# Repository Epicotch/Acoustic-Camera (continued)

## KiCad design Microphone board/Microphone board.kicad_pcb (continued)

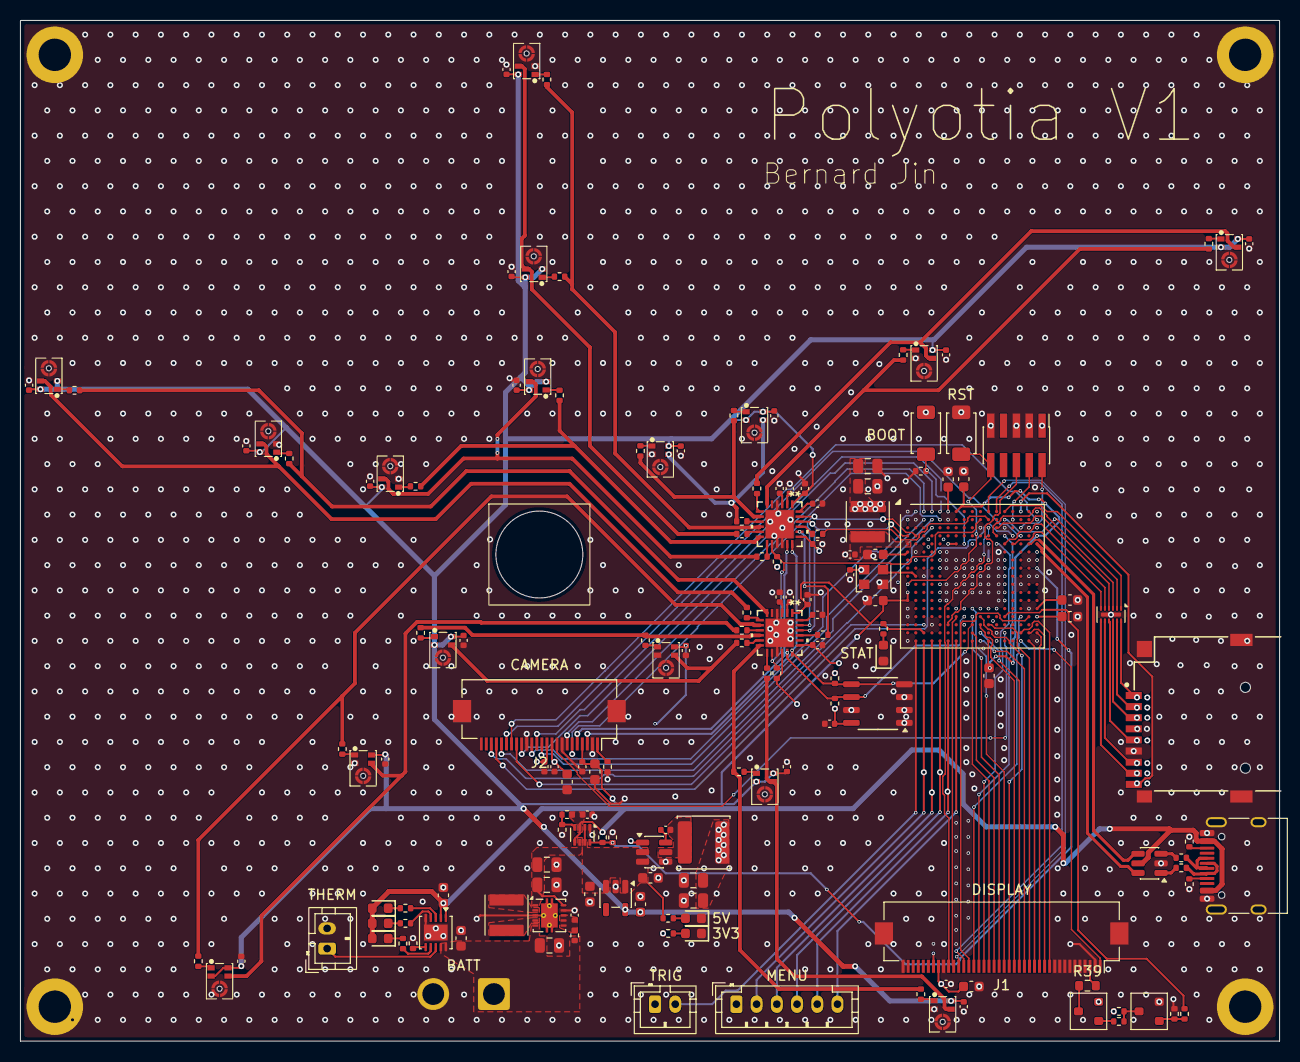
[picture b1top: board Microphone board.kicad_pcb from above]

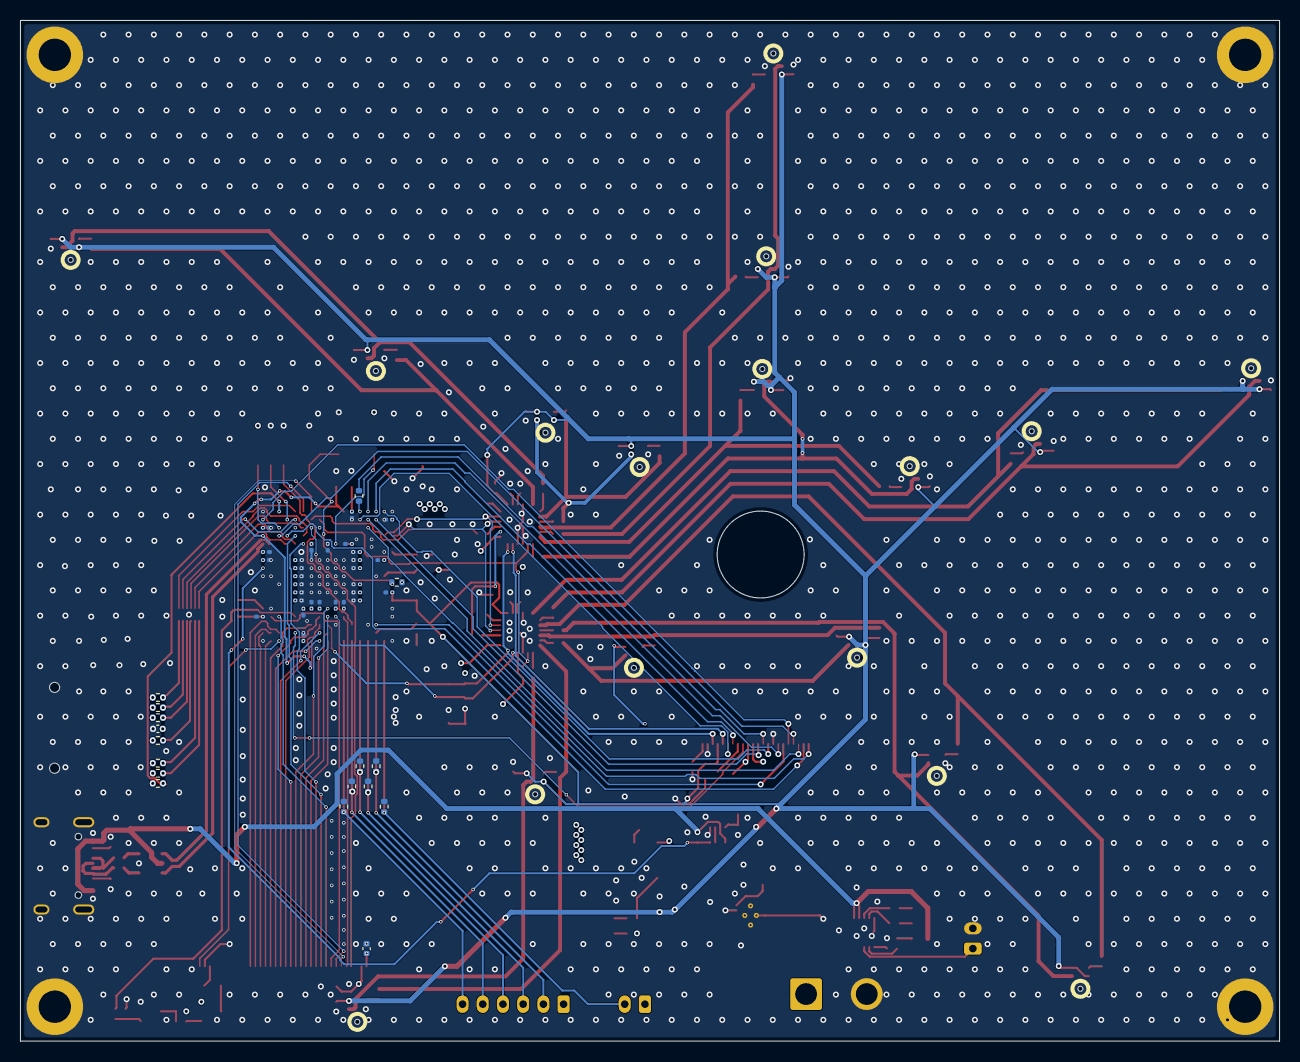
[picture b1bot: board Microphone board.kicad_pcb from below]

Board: 4 copper layers, 124.6 x 101.0 mm, 212 parts (46 on the bottom side), 161 nets.

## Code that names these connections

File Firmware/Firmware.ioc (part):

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Mcu.Name=STM32H747XIHx
Mcu.Package=TFBGA240
Mcu.UserName=STM32H747XIHx
PA0_C.GPIOParameters=PinAttribute
PA0_C.PinAttribute=CortexM4
PA0_C.Signal=ADCx_INP0
PA10.GPIOParameters=PinAttribute
PA10.Mode=Slave_8_bits_External_Synchro
PA10.PinAttribute=CortexM4
PA10.Signal=DCMI_D1
PA11.GPIOParameters=PinAttribute
PA11.Mode=Device_Only
PA11.PinAttribute=CortexM4
PA11.Signal=USB_OTG_FS_DM
PA12.GPIOParameters=PinAttribute
PA12.Mode=Device_Only
PA12.PinAttribute=CortexM4
PA12.Signal=USB_OTG_FS_DP
PA13\ (JTMS/SWDIO).GPIOParameters=PinAttribute
PA13\ (JTMS/SWDIO).Mode=Trace_Asynchronous_SW
PA13\ (JTMS/SWDIO).PinAttribute=CortexM7
PA13\ (JTMS/SWDIO).Signal=DEBUG_JTMS-SWDIO
PA14\ (JTCK/SWCLK).GPIOParameters=PinAttribute
PA14\ (JTCK/SWCLK).Mode=Trace_Asynchronous_SW
PA14\ (JTCK/SWCLK).PinAttribute=CortexM7
PA14\ (JTCK/SWCLK).Signal=DEBUG_JTCK-SWCLK
PA3.ContextOwner=CortexM4
PA3.GPIOParameters=GPIO_Label,PinAttribute
PA3.GPIO_Label=TRIGGER
PA3.PinAttribute=CortexM4
PA3.Signal=GPIO_Input
PA4.ContextOwner=CortexM4
PA4.GPIOParameters=GPIO_Label,PinAttribute
PA4.GPIO_Label=LEFT
PA4.PinAttribute=CortexM4
PA4.Signal=GPIO_Input
PA5.ContextOwner=CortexM4
PA5.GPIOParameters=GPIO_Label,PinAttribute
PA5.GPIO_Label=STATUS_LED
PA5.PinAttribute=CortexM4
PA5.Signal=GPIO_Output
PA6.GPIOParameters=PinAttribute
PA6.Mode=Slave_8_bits_External_Synchro
PA6.PinAttribute=CortexM4
PA6.Signal=DCMI_PIXCLK
PA9.GPIOParameters=PinAttribute
PA9.Mode=Slave_8_bits_External_Synchro
PA9.PinAttribute=CortexM4
PA9.Signal=DCMI_D0
PB0.ContextOwner=CortexM4
PB0.GPIOParameters=GPIO_Label,PinAttribute
PB0.GPIO_Label=BUTTON
PB0.PinAttribute=CortexM4
PB0.Signal=GPIO_Input
PB14.ContextOwner=CortexM4
PB14.GPIOParameters=GPIO_Label,PinAttribute
PB14.GPIO_Label=TEAR
PB14.PinAttribute=CortexM4
PB14.Signal=GPXTI14
PB15.ContextOwner=CortexM4
PB15.GPIOParameters=GPIO_PuPd,GPIO_Label,PinAttribute
PB15.GPIO_Label=LCD_RST
PB15.GPIO_PuPd=GPIO_PULLUP
PB15.PinAttribute=CortexM4
PB15.Signal=GPIO_Output
PB3\ (JTDO/TRACESWO).GPIOParameters=PinAttribute
PB3\ (JTDO/TRACESWO).Mode=Trace_Asynchronous_SW
PB3\ (JTDO/TRACESWO).PinAttribute=CortexM7
PB3\ (JTDO/TRACESWO).Signal=DEBUG_JTDO-SWO
PB5.GPIOParameters=PinAttribute
PB5.PinAttribute=CortexM4
PB5.Signal=S_TIM3_CH2
PB6.ContextOwner=CortexM4
PB6.GPIOParameters=GPIO_PuPd,GPIO_Label,PinAttribute
PB6.GPIO_Label=CAM_RST
PB6.GPIO_PuPd=GPIO_PULLUP
PB6.PinAttribute=CortexM4
PB6.Signal=GPIO_Output
PC10.GPIOParameters=PinAttribute
PC10.Mode=SD_4_bits_Wide_bus
PC10.PinAttribute=CortexM7
PC10.Signal=SDMMC1_D2
PC11.GPIOParameters=PinAttribute
PC11.Mode=SD_4_bits_Wide_bus
PC11.PinAttribute=CortexM7
PC11.Signal=SDMMC1_D3
PC12.GPIOParameters=PinAttribute
PC12.Mode=SD_4_bits_Wide_bus
PC12.PinAttribute=CortexM7
PC12.Signal=SDMMC1_CK
PC5.ContextOwner=CortexM4
PC5.GPIOParameters=GPIO_Label,PinAttribute
PC5.GPIO_Label=DOWN
PC5.PinAttribute=CortexM4
PC5.Signal=GPIO_Input
PC8.GPIOParameters=PinAttribute
PC8.Mode=SD_4_bits_Wide_bus
PC8.PinAttribute=CortexM7
PC8.Signal=SDMMC1_D0
PC9.GPIOParameters=PinAttribute
PC9.Mode=SD_4_bits_Wide_bus
PC9.PinAttribute=CortexM7
PC9.Signal=SDMMC1_D1
PD0.GPIOParameters=PinAttribute
PD0.PinAttribute=CortexM4
PD0.Signal=FMC_D2_DA2
PD1.GPIOParameters=PinAttribute
PD1.PinAttribute=CortexM4
PD1.Signal=FMC_D3_DA3
PD10.GPIOParameters=PinAttribute
PD10.PinAttribute=CortexM4
PD10.Signal=FMC_D15_DA15
PD14.GPIOParameters=PinAttribute
PD14.PinAttribute=CortexM4
PD14.Signal=FMC_D0_DA0
PD15.GPIOParameters=PinAttribute
PD15.PinAttribute=CortexM4
PD15.Signal=FMC_D1_DA1
PD2.GPIOParameters=PinAttribute
PD2.Mode=SD_4_bits_Wide_bus
PD2.PinAttribute=CortexM7
PD2.Signal=SDMMC1_CMD
PD4.GPIOParameters=PinAttribute
PD4.PinAttribute=CortexM4
PD4.Signal=FMC_NOE
PD5.GPIOParameters=PinAttribute
PD5.PinAttribute=CortexM4
PD5.Signal=FMC_NWE
PD6.GPIOParameters=GPIO_Speed,GPIO_PuPd,PinAttribute,GPIO_Mode
PD6.GPIO_Mode=GPIO_MODE_AF_PP
PD6.GPIO_PuPd=GPIO_NOPULL
PD6.GPIO_Speed=GPIO_SPEED_FREQ_LOW
PD6.Mode=SAI_A_Master
PD6.PinAttribute=CortexM7
PD6.Signal=SAI1_SD_A
PD7.GPIOParameters=PinAttribute
PD7.Mode=NorPsramChipSelect1_1
PD7.PinAttribute=CortexM4
PD7.Signal=FMC_NE1
PD8.GPIOParameters=PinAttribute
PD8.PinAttribute=CortexM4
PD8.Signal=FMC_D13_DA13
PD9.GPIOParameters=PinAttribute
PD9.PinAttribute=CortexM4
PD9.Signal=FMC_D14_DA14
PE0.GPIOParameters=PinAttribute
PE0.Mode=Slave_8_bits_External_Synchro
PE0.PinAttribute=CortexM4
PE0.Signal=DCMI_D2
PE1.GPIOParameters=PinAttribute
PE1.Mode=Slave_8_bits_External_Synchro
PE1.PinAttribute=CortexM4
PE1.Signal=DCMI_D3
PE10.GPIOParameters=PinAttribute
PE10.PinAttribute=CortexM4
PE10.Signal=FMC_D7_DA7
PE11.GPIOParameters=PinAttribute
PE11.PinAttribute=CortexM4
PE11.Signal=FMC_D8_DA8
PE12.GPIOParameters=PinAttribute
PE12.PinAttribute=CortexM4
PE12.Signal=FMC_D9_DA9
PE13.GPIOParameters=PinAttribute
PE13.PinAttribute=CortexM4
PE13.Signal=FMC_D10_DA10
PE14.GPIOParameters=PinAttribute
PE14.PinAttribute=CortexM4
PE14.Signal=FMC_D11_DA11
PE15.GPIOParameters=PinAttribute
PE15.PinAttribute=CortexM4
PE15.Signal=FMC_D12_DA12
PE4.GPIOParameters=GPIO_Speed,GPIO_PuPd,PinAttribute,GPIO_Mode
PE4.GPIO_Mode=GPIO_MODE_AF_PP
PE4.GPIO_PuPd=GPIO_NOPULL
PE4.GPIO_Speed=GPIO_SPEED_FREQ_LOW
PE4.Mode=SAI_A_Master
PE4.PinAttribute=CortexM7
PE4.Signal=SAI1_FS_A
PE5.GPIOParameters=GPIO_Speed,GPIO_PuPd,PinAttribute,GPIO_Mode
PE5.GPIO_Mode=GPIO_MODE_AF_PP
PE5.GPIO_PuPd=GPIO_NOPULL
PE5.GPIO_Speed=GPIO_SPEED_FREQ_LOW
PE5.Mode=SAI_A_Master
PE5.PinAttribute=CortexM7
PE5.Signal=SAI1_SCK_A
PE7.GPIOParameters=PinAttribute
PE7.PinAttribute=CortexM4
PE7.Signal=FMC_D4_DA4
PE8.GPIOParameters=PinAttribute
PE8.PinAttribute=CortexM4
PE8.Signal=FMC_D5_DA5
PE9.GPIOParameters=PinAttribute
PE9.PinAttribute=CortexM4
PE9.Signal=FMC_D6_DA6
PF13.GPIOParameters=PinAttribute
PF13.PinAttribute=CortexM4
PF13.Signal=FMC_A7
PF14.GPIOParameters=PinAttribute
PF14.Mode=I2C
PF14.PinAttribute=CortexM7
PF14.Signal=I2C4_SCL
PF15.GPIOParameters=PinAttribute
PF15.Mode=I2C
PF15.PinAttribute=CortexM7
PF15.Signal=I2C4_SDA
PH0-OSC_IN\ (PH0).GPIOParameters=PinAttribute
PH0-OSC_IN\ (PH0).Mode=HSE-External-Clock-Source
PH0-OSC_IN\ (PH0).PinAttribute=Free
PH0-OSC_IN\ (PH0).Signal=RCC_OSC_IN
PH10.GPIOParameters=GPIO_Label,PinAttribute
PH10.GPIO_Label=BACKLIGHT
PH10.PinAttribute=CortexM4
PH10.Signal=S_TIM5_CH1
PH14.GPIOParameters=PinAttribute
PH14.Mode=Slave_8_bits_External_Synchro
PH14.PinAttribute=CortexM4
PH14.Signal=DCMI_D4
PH8.GPIOParameters=PinAttribute
PH8.Mode=Slave_8_bits_External_Synchro
PH8.PinAttribute=CortexM4
PH8.Signal=DCMI_HSYNC
PI1.GPIOParameters=GPIO_Label,PinAttribute
PI1.GPIO_Label=SDMMC_DET
PI1.PinAttribute=Free
PI1.Signal=GPIO_Input
PI4.GPIOParameters=PinAttribute
PI4.Mode=Slave_8_bits_External_Synchro
PI4.PinAttribute=CortexM4
PI4.Signal=DCMI_D5
PI5.GPIOParameters=PinAttribute
PI5.Mode=Slave_8_bits_External_Synchro
PI5.PinAttribute=CortexM4
PI5.Signal=DCMI_VSYNC
PI6.GPIOParameters=PinAttribute
PI6.Mode=Slave_8_bits_External_Synchro
PI6.PinAttribute=CortexM4
PI6.Signal=DCMI_D6
PI7.GPIOParameters=PinAttribute
PI7.Mode=Slave_8_bits_External_Synchro
PI7.PinAttribute=CortexM4
PI7.Signal=DCMI_D7
PJ15.ContextOwner=CortexM7
PJ15.GPIOParameters=GPIO_Label,PinAttribute
PJ15.GPIO_Label=SHDNZ
PJ15.PinAttribute=CortexM7
PJ15.Signal=GPIO_Output
PJ3.ContextOwner=CortexM4
PJ3.GPIOParameters=GPIO_Label,PinAttribute
PJ3.GPIO_Label=RIGHT
PJ3.PinAttribute=CortexM4
PJ3.Signal=GPIO_Input
PJ4.ContextOwner=CortexM4
PJ4.GPIOParameters=GPIO_Label,PinAttribute
PJ4.GPIO_Label=UP
PJ4.PinAttribute=CortexM4
PJ4.Signal=GPIO_Input
PK2.ContextOwner=CortexM4
PK2.GPIOParameters=GPIO_Label,PinAttribute
PK2.GPIO_Label=POWER_STATUS
PK2.PinAttribute=CortexM4
PK2.Signal=GPIO_Input
RCC.SYSCLKFreq_VALUE=480000000
RCC.SYSCLKSource=RCC_SYSCLKSOURCE_PLLCLK
board=custom

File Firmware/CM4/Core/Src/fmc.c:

/* USER CODE BEGIN Header */
/**
  ******************************************************************************
  * File Name          : FMC.c
  * Description        : This file provides code for the configuration
  *                      of the FMC peripheral.
  ******************************************************************************
  * @attention
  *
  * Copyright (c) 2026 STMicroelectronics.
  * All rights reserved.
  *
  * This software is licensed under terms that can be found in the LICENSE file
  * in the root directory of this software component.
  * If no LICENSE file comes with this software, it is provided AS-IS.
  *
  ******************************************************************************
  */
/* USER CODE END Header */

/* Includes ------------------------------------------------------------------*/
#include "fmc.h"

/* USER CODE BEGIN 0 */

/* USER CODE END 0 */

SRAM_HandleTypeDef hsram1;

/* FMC initialization function */
void MX_FMC_Init(void)
{
  /* USER CODE BEGIN FMC_Init 0 */

  /* USER CODE END FMC_Init 0 */

  FMC_NORSRAM_TimingTypeDef Timing = {0};

  /* USER CODE BEGIN FMC_Init 1 */

  /* USER CODE END FMC_Init 1 */

  /** Perform the SRAM1 memory initialization sequence
  */
  hsram1.Instance = FMC_NORSRAM_DEVICE;
  hsram1.Extended = FMC_NORSRAM_EXTENDED_DEVICE;
  /* hsram1.Init */
  hsram1.Init.NSBank = FMC_NORSRAM_BANK1;
  hsram1.Init.DataAddressMux = FMC_DATA_ADDRESS_MUX_DISABLE;
  hsram1.Init.MemoryType = FMC_MEMORY_TYPE_SRAM;
  hsram1.Init.MemoryDataWidth = FMC_NORSRAM_MEM_BUS_WIDTH_16;
  hsram1.Init.BurstAccessMode = FMC_BURST_ACCESS_MODE_DISABLE;
  hsram1.Init.WaitSignalPolarity = FMC_WAIT_SIGNAL_POLARITY_LOW;
  hsram1.Init.WaitSignalActive = FMC_WAIT_TIMING_BEFORE_WS;
  hsram1.Init.WriteOperation = FMC_WRITE_OPERATION_ENABLE;
  hsram1.Init.WaitSignal = FMC_WAIT_SIGNAL_DISABLE;
  hsram1.Init.ExtendedMode = FMC_EXTENDED_MODE_DISABLE;
  hsram1.Init.AsynchronousWait = FMC_ASYNCHRONOUS_WAIT_DISABLE;
  hsram1.Init.WriteBurst = FMC_WRITE_BURST_DISABLE;
  hsram1.Init.ContinuousClock = FMC_CONTINUOUS_CLOCK_SYNC_ONLY;
  hsram1.Init.WriteFifo = FMC_WRITE_FIFO_ENABLE;
  hsram1.Init.PageSize = FMC_PAGE_SIZE_NONE;
  /* Timing */
  Timing.AddressSetupTime = 15;
  Timing.AddressHoldTime = 15;
  Timing.DataSetupTime = 255;
  Timing.BusTurnAroundDuration = 15;
  Timing.CLKDivision = 16;
  Timing.DataLatency = 17;
  Timing.AccessMode = FMC_ACCESS_MODE_A;
  /* ExtTiming */

  if (HAL_SRAM_Init(&hsram1, &Timing, NULL) != HAL_OK)
  {
    Error_Handler( );
  }

  /* USER CODE BEGIN FMC_Init 2 */

  /* USER CODE END FMC_Init 2 */
}

static uint32_t FMC_Initialized = 0;

static void HAL_FMC_MspInit(void){
  /* USER CODE BEGIN FMC_MspInit 0 */

  /* USER CODE END FMC_MspInit 0 */
  GPIO_InitTypeDef GPIO_InitStruct = {0};
  if (FMC_Initialized) {
    return;
  }
  FMC_Initialized = 1;
  RCC_PeriphCLKInitTypeDef PeriphClkInitStruct = {0};

  /** Initializes the peripherals clock
  */
    PeriphClkInitStruct.PeriphClockSelection = RCC_PERIPHCLK_FMC;
    PeriphClkInitStruct.FmcClockSelection = RCC_FMCCLKSOURCE_D1HCLK;
    if (HAL_RCCEx_PeriphCLKConfig(&PeriphClkInitStruct) != HAL_OK)
    {
      Error_Handler();
    }

  /* Peripheral clock enable */
  __HAL_RCC_FMC_CLK_ENABLE();

  /** FMC GPIO Configuration
  PD5   ------> FMC_NWE
  PD4   ------> FMC_NOE
  PD7   ------> FMC_NE1
  PD0   ------> FMC_D2
  PD1   ------> FMC_D3
  PE10   ------> FMC_D7
  PF13   ------> FMC_A7
  PE9   ------> FMC_D6
  PE11   ------> FMC_D8
  PD15   ------> FMC_D1
  PD14   ------> FMC_D0
  PE12   ------> FMC_D9
  PE15   ------> FMC_D12
  PE8   ------> FMC_D5
  PE13   ------> FMC_D10
  PD10   ------> FMC_D15
  PD9   ------> FMC_D14
  PE7   ------> FMC_D4
  PE14   ------> FMC_D11
  PD8   ------> FMC_D13
  */
  /* GPIO_InitStruct */
  GPIO_InitStruct.Pin = GPIO_PIN_5|GPIO_PIN_4|GPIO_PIN_7|GPIO_PIN_0
                          |GPIO_PIN_1|GPIO_PIN_15|GPIO_PIN_14|GPIO_PIN_10
                          |GPIO_PIN_9|GPIO_PIN_8;
  GPIO_InitStruct.Mode = GPIO_MODE_AF_PP;
  GPIO_InitStruct.Pull = GPIO_NOPULL;
  GPIO_InitStruct.Speed = GPIO_SPEED_FREQ_VERY_HIGH;
  GPIO_InitStruct.Alternate = GPIO_AF12_FMC;

  HAL_GPIO_Init(GPIOD, &GPIO_InitStruct);

  /* GPIO_InitStruct */
  GPIO_InitStruct.Pin = GPIO_PIN_10|GPIO_PIN_9|GPIO_PIN_11|GPIO_PIN_12
                          |GPIO_PIN_15|GPIO_PIN_8|GPIO_PIN_13|GPIO_PIN_7
                          |GPIO_PIN_14;
  GPIO_InitStruct.Mode = GPIO_MODE_AF_PP;
  GPIO_InitStruct.Pull = GPIO_NOPULL;
  GPIO_InitStruct.Speed = GPIO_SPEED_FREQ_VERY_HIGH;
  GPIO_InitStruct.Alternate = GPIO_AF12_FMC;

  HAL_GPIO_Init(GPIOE, &GPIO_InitStruct);

  /* GPIO_InitStruct */
  GPIO_InitStruct.Pin = GPIO_PIN_13;
  GPIO_InitStruct.Mode = GPIO_MODE_AF_PP;
  GPIO_InitStruct.Pull = GPIO_NOPULL;
  GPIO_InitStruct.Speed = GPIO_SPEED_FREQ_VERY_HIGH;
  GPIO_InitStruct.Alternate = GPIO_AF12_FMC;

  HAL_GPIO_Init(GPIOF, &GPIO_InitStruct);

  /* USER CODE BEGIN FMC_MspInit 1 */

  /* USER CODE END FMC_MspInit 1 */
}

void HAL_SRAM_MspInit(SRAM_HandleTypeDef* sramHandle){
  /* USER CODE BEGIN SRAM_MspInit 0 */

  /* USER CODE END SRAM_MspInit 0 */
  HAL_FMC_MspInit();
  /* USER CODE BEGIN SRAM_MspInit 1 */

  /* USER CODE END SRAM_MspInit 1 */
}

static uint32_t FMC_DeInitialized = 0;

static void HAL_FMC_MspDeInit(void){
  /* USER CODE BEGIN FMC_MspDeInit 0 */

  /* USER CODE END FMC_MspDeInit 0 */
  if (FMC_DeInitialized) {
    return;
  }
  FMC_DeInitialized = 1;
  /* Peripheral clock enable */
  __HAL_RCC_FMC_CLK_DISABLE();

  /** FMC GPIO Configuration
  PD5   ------> FMC_NWE
  PD4   ------> FMC_NOE
  PD7   ------> FMC_NE1
  PD0   ------> FMC_D2
  PD1   ------> FMC_D3
  PE10   ------> FMC_D7
  PF13   ------> FMC_A7
  PE9   ------> FMC_D6
  PE11   ------> FMC_D8
  PD15   ------> FMC_D1
  PD14   ------> FMC_D0
  PE12   ------> FMC_D9
  PE15   ------> FMC_D12
  PE8   ------> FMC_D5
  PE13   ------> FMC_D10
  PD10   ------> FMC_D15
  PD9   ------> FMC_D14
  PE7   ------> FMC_D4
  PE14   ------> FMC_D11
  PD8   ------> FMC_D13
  */

  HAL_GPIO_DeInit(GPIOD, GPIO_PIN_5|GPIO_PIN_4|GPIO_PIN_7|GPIO_PIN_0
                          |GPIO_PIN_1|GPIO_PIN_15|GPIO_PIN_14|GPIO_PIN_10
                          |GPIO_PIN_9|GPIO_PIN_8);

  HAL_GPIO_DeInit(GPIOE, GPIO_PIN_10|GPIO_PIN_9|GPIO_PIN_11|GPIO_PIN_12
                          |GPIO_PIN_15|GPIO_PIN_8|GPIO_PIN_13|GPIO_PIN_7
                          |GPIO_PIN_14);

  HAL_GPIO_DeInit(GPIOF, GPIO_PIN_13);

  /* USER CODE BEGIN FMC_MspDeInit 1 */

  /* USER CODE END FMC_MspDeInit 1 */
}

void HAL_SRAM_MspDeInit(SRAM_HandleTypeDef* sramHandle){
  /* USER CODE BEGIN SRAM_MspDeInit 0 */

  /* USER CODE END SRAM_MspDeInit 0 */
  HAL_FMC_MspDeInit();
  /* USER CODE BEGIN SRAM_MspDeInit 1 */

  /* USER CODE END SRAM_MspDeInit 1 */
}
/**
  * @}
  */

/**
  * @}
  */

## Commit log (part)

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2026-06-04 baby steps
2026-06-08 Made almost the rest of the schematic lol
2026-06-08 almost finished power
2026-06-10 PCB routed
2026-06-11 finished r1 of the board
2026-06-13 widened traces
2026-06-27 Updated project firmware
